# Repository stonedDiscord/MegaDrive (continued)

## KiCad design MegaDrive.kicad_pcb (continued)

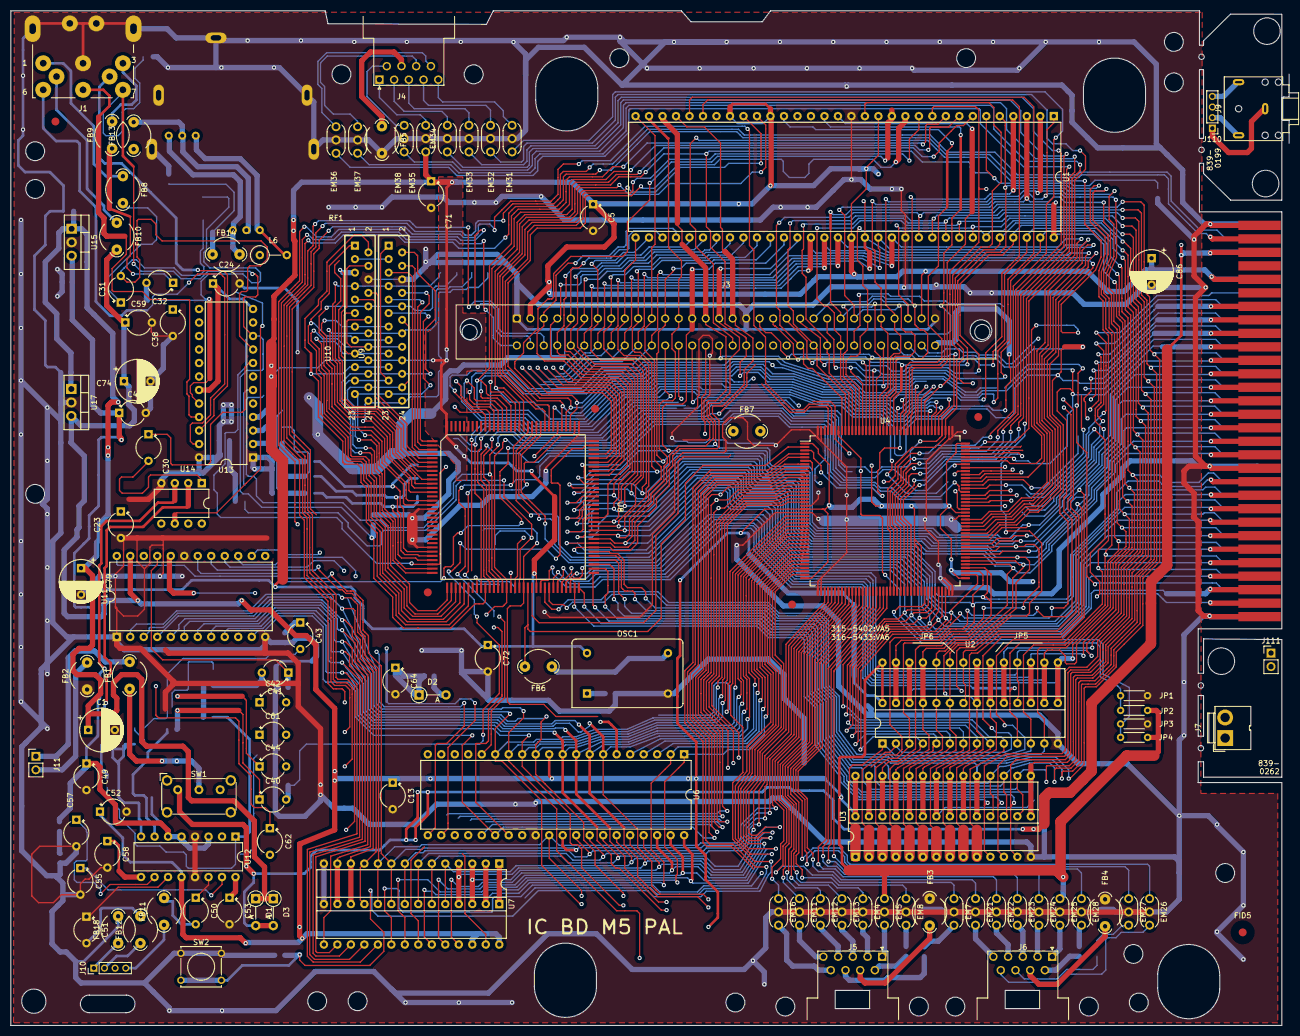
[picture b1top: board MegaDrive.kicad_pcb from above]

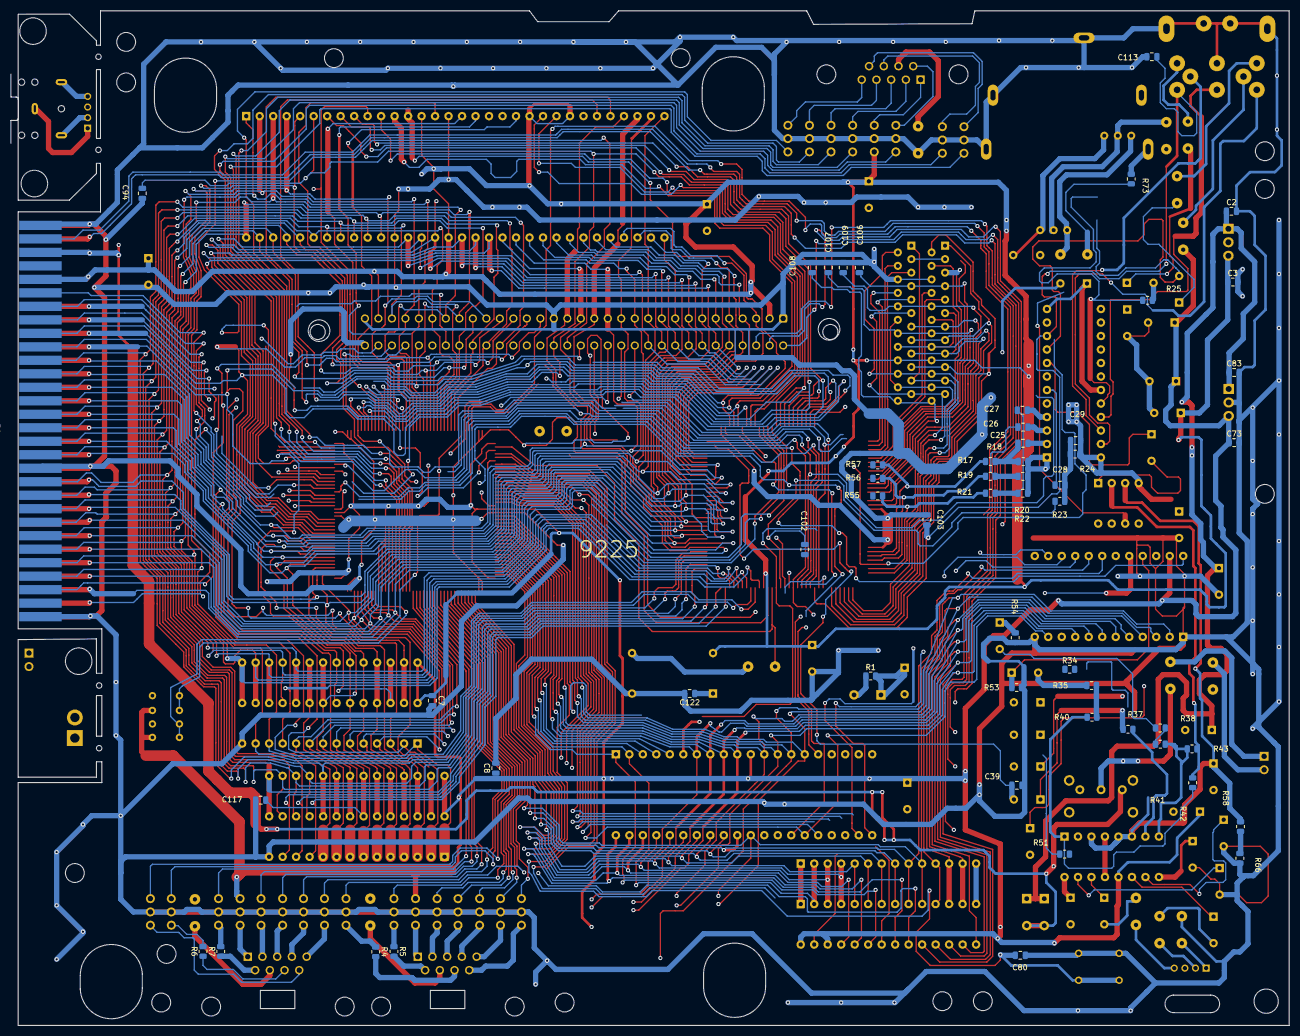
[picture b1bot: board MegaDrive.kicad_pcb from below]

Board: 2 copper layers, 240.6 x 191.0 mm, 170 parts (55 on the bottom side), 244 nets.

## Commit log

2024-02-23 init
2024-03-03 finalize
2024-03-03 measurements on wrong layer
2024-03-03 pour on the audio board
2024-03-05 fix hole overlap
2024-03-13 use D-sub connctors that can be ordered
2024-03-14 missing resistor and bom fixup
2024-03-20 fix some cap values and probably mess some up
2024-03-22 add silkscreen so no one else rotates their vdp
2025-05-02 linguist override
2025-05-02 do not try this footprint trick
2025-12-30 larger qfp footprint
2025-12-30 missing zclk connection
2025-12-30 cant recommend getting this done by a board house
